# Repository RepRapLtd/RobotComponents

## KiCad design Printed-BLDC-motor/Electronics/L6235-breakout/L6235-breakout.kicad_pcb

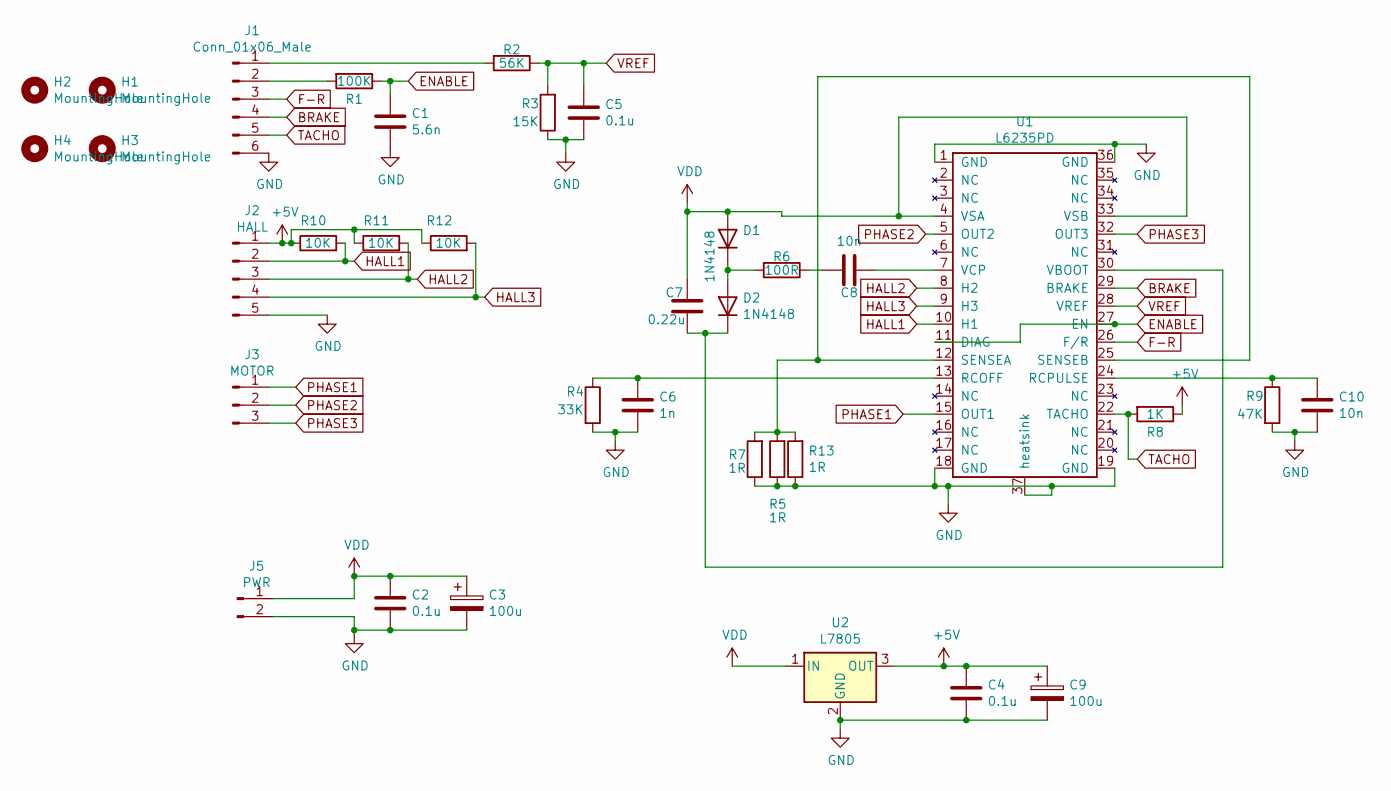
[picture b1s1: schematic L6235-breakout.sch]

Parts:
C1: 5.6n; C_0805_2012Metric
C2, C4, C5: 0.1u; C_0805_2012Metric
C3, C9: 100u; C_Radial_D8.0mm_H7.0mm_P3.50mm
C6: 1n; C_0805_2012Metric
C7: 0.22u; C_0805_2012Metric
C8, C10: 10n; C_0805_2012Metric
D1, D2: 1N4148; D_0805_2012Metric
H1, H2, H3, H4: MountingHole; MountingHole_3.2mm_M3
J1: Conn_01x06_Male; PinHeader_1x06_P2.54mm_Vertical
J2: HALL; PinHeader_1x05_P2.54mm_Vertical
J3: MOTOR; PinHeader_1x03_P2.54mm_Vertical
J5: PWR; PinHeader_1x02_P2.54mm_Vertical
R1: 100K; R_0805_2012Metric
R2: 56K; R_0805_2012Metric
R3: 15K; R_0805_2012Metric
R4: 33K; R_0805_2012Metric
R5, R7, R13: 1R; R_0805_2012Metric
R6: 100R; R_0805_2012Metric
R8: 1K; R_0805_2012Metric
R9: 47K; R_0805_2012Metric
R10, R11, R12: 10K; R_0805_2012Metric
U1: L6235PD; SOIC-36_11mmx16mmx3.6mm
U2: L7805; TO-252-2

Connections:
+5V: C4.1, C9.1, J2.1, R8.1, R10.1, R11.1, R12.1, U2.3 (OUT)
BRAKE: J1.4, U1.29 (BRAKE)
ENABLE: C1.1, R1.1, U1.11 (DIAG), U1.27 (EN)
F-R: J1.3, U1.26 (F/R)
GND: C1.2, C2.2, C3.2, C4.2, C5.2, C6.2, C9.2, C10.2, J1.6, J2.5, J5.2, R3.1, R4.2, R5.1, R7.1, R9.2, R13.1, U1.1 (GND), U1.18 (GND), U1.19 (GND), U1.36 (GND), U1.37 (heatsink), U2.2 (GND)
HALL1: J2.2, R10.2, U1.10 (H1)
HALL2: J2.3, R11.2, U1.8 (H2)
HALL3: J2.4, R12.2, U1.9 (H3)
unnamed: C6.1, R4.1, U1.13 (RCOFF)
unnamed: C7.2, D2.1 (K), U1.30 (VBOOT)
unnamed: C8.1, U1.7 (VCP)
unnamed: C8.2, R6.1
unnamed: C10.1, R9.1, U1.24 (RCPULSE)
unnamed: D1.1 (K), D2.2 (A), R6.2
unnamed: J1.1, R2.2
unnamed: J1.2, R1.2
unnamed: R5.2, R7.2, R13.2, U1.12 (SENSEA), U1.25 (SENSEB)
PHASE1: J3.1, U1.15 (OUT1)
PHASE2: J3.2, U1.5 (OUT2)
PHASE3: J3.3, U1.32 (OUT3)
TACHO: J1.5, R8.2, U1.22 (TACHO)
VDD: C2.1, C3.1, C7.1, D1.2 (A), J5.1, U1.4 (VSA), U1.33 (VSB), U2.1 (IN)
VREF: C5.1, R2.1, R3.2, U1.28 (VREF)

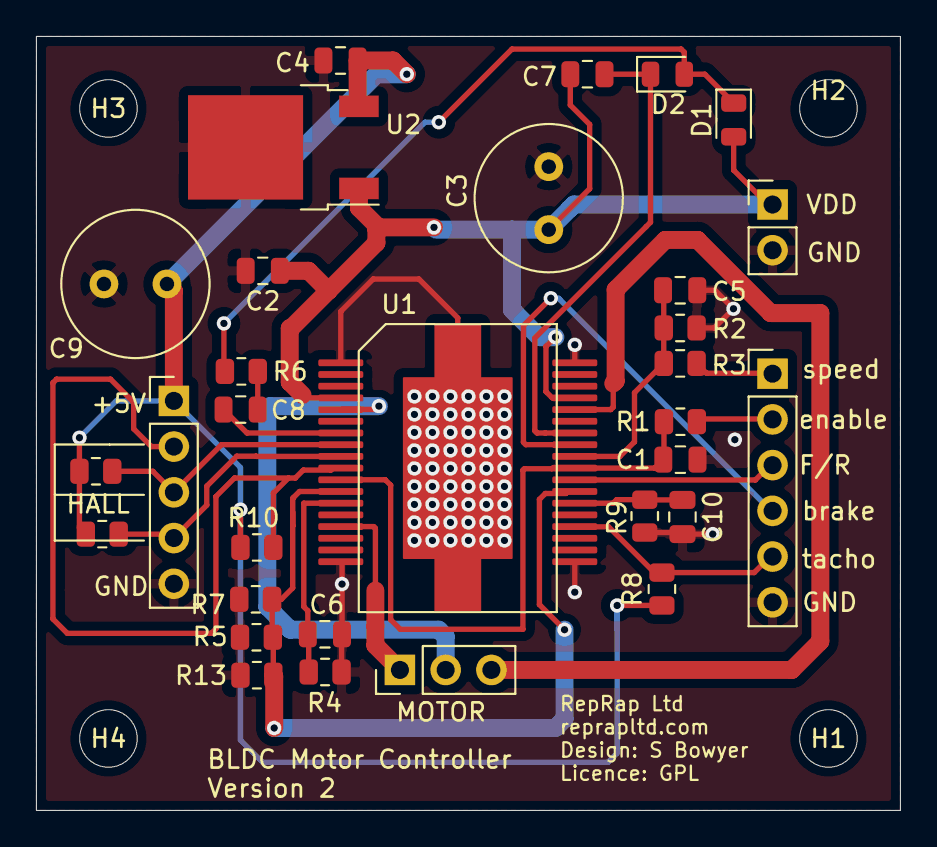
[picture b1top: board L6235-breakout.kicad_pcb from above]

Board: 2 copper layers, 48.0 x 43.0 mm, 35 parts (0 on the bottom side), 23 nets.

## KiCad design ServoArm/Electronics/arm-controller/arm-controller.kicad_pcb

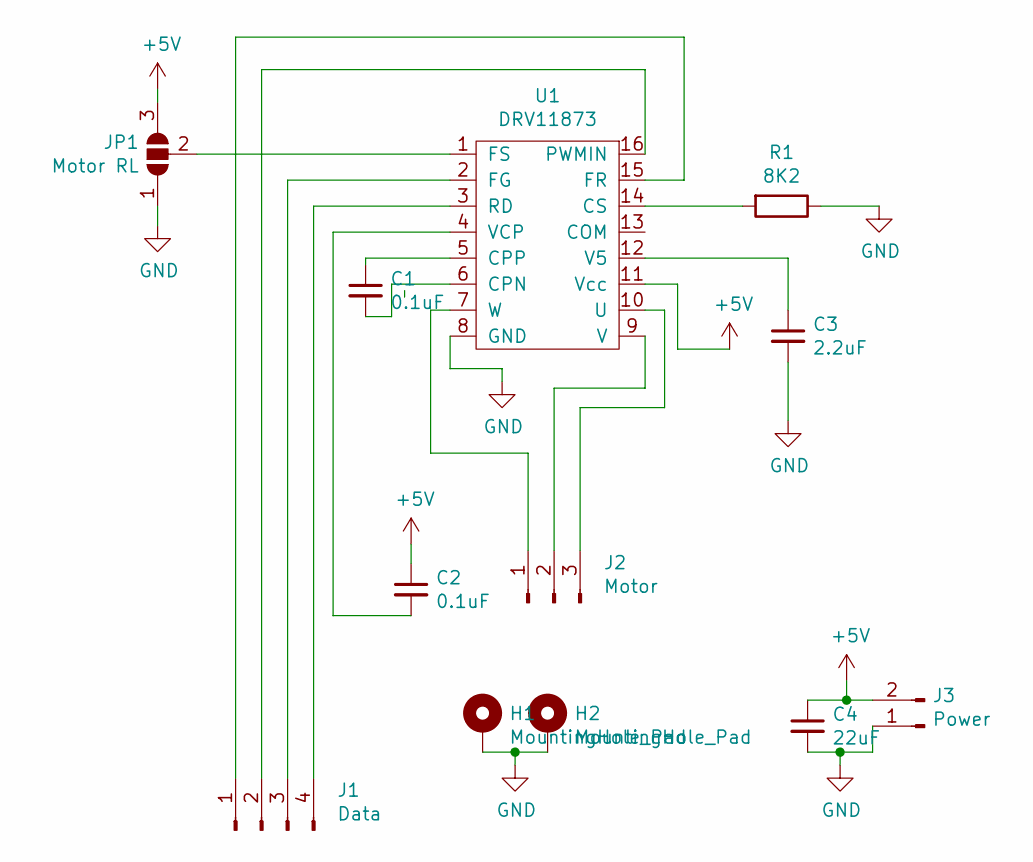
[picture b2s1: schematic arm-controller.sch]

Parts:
C1, C2: 0.1uF; C_0805_2012Metric
C3: 2.2uF; C_0805_2012Metric
C4: 22uF; C_0805_2012Metric
H1, H2: MountingHole_Pad; MountingHole_2.7mm
J1: Data; PinHeader_1x04_P2.54mm_Vertical
J2: Motor; PinHeader_1x03_P2.54mm_Vertical
J3: Power; PinHeader_1x02_P2.54mm_Vertical
JP1: Motor RL; SolderJumper-3_P1.3mm_Open_Pad1.0x1.5mm
R1: 8K2; R_0805_2012Metric
U1: DRV11873; TSSOP-16-1EP_4.4x5mm_P0.65mm

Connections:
+5V: C2.1, C4.1, J3.2, JP1.3 (B), U1.11 (Vcc)
GND: C3.2, C4.2, H1.1, H2.1, J3.1, JP1.1 (A), R1.1, U1.8 (GND)
unnamed: C1.1, U1.5 (CPP)
unnamed: C1.2, U1.6 (CPN)
unnamed: C2.2, U1.4 (VCP)
unnamed: C3.1, U1.12 (V5)
unnamed: J1.1, U1.15 (FR)
unnamed: J1.2, U1.16 (PWMIN)
unnamed: J1.3, U1.2 (FG)
unnamed: J1.4, U1.3 (RD)
unnamed: J2.1, U1.7 (W)
unnamed: J2.2, U1.9 (V)
unnamed: J2.3, U1.10 (U)
unnamed: JP1.2 (C), U1.1 (FS)
unnamed: R1.2, U1.14 (CS)

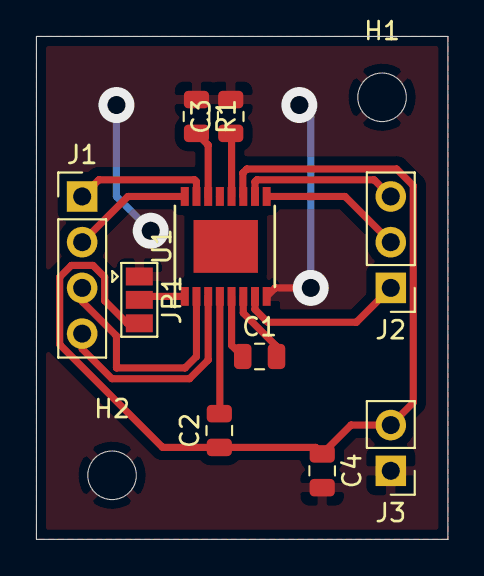
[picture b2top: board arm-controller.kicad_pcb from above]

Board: 2 copper layers, 22.9 x 27.9 mm, 12 parts (0 on the bottom side), 15 nets.

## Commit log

2021-03-15 First commit.
2021-03-16 Corrected gearbox design.
2021-03-17 WIP gearbox and drive.
2021-03-18 WIP.
2021-03-19 Arm WIP.
2021-03-25 First, but not complete, version of the servo.
2021-03-26 First complete (?) servo design.
2021-03-26 Tweaked design...
2021-03-27 Small dimensional adjustments.
2021-03-28 Minor dimension corrections.
2021-03-29 Servo control program started.
2021-03-30 Sally started on a Ravigneaux servo. PID test program WIP.
2021-03-31 Tidyibg the servo program. WIP.
2021-04-01 More rav work (SB). Improved servo prog (AB).
2021-04-13 Various bits of WIP.
2021-04-14 First hack at the printable BLDC motor.
2021-04-27 More details of the BLDC motor completed.
2021-04-29 Added wire drum counter design to measure windings onto the coils.
2021-04-30 First version of coild counter working. Improved sun gear design.
2021-09-29 Playing around with cycloidal gear designs...
2021-09-30 Offset cycloid program coming along. Not yet finished.
2021-09-30 cycloidal drive program fully working
2021-09-30 Further enhancements...
2021-10-01 Blog post files added.
2021-10-01 Comment tidying.
2021-10-01 Spelling...
2021-10-01 More tidying...
2021-10-01 Started design of whole cycloidal gearbox.
2021-10-01 Tidying.
2021-10-02 Started adding code to creat a lip to constrain axial movement.
2021-10-02 Code to optionally create restraining lip added. Seems to work.
2021-10-02 Gearbox changed to take advantage of new code.
2021-10-04 Initial design of motor controller.
2021-10-07 Gearbox and L6235 updates.
2021-10-08 README for cycloidal gearbox.
2021-10-08 Editing README...
2021-10-08 More edits.
2021-10-08 Edit...
2021-10-08 Edit
2021-10-08 Added video
2021-10-15 Latest version of Sally's L6235-breakout
2021-10-20 Latest BLDC driver PCB.
2021-10-27 Added BOM.
2022-01-17 Footprint of TO-220 7805 corrected.
2022-01-18 Controller PCB updated to Version 2.
2022-01-19 Added ground reference to control connector.
2022-01-19 Added Arduino prog for the motor control board.
2022-01-20 Fixed missing chip connetions.
2022-02-09 V2 PCB send for trial production.

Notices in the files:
Printed-BLDC-motor/Electronics/L6235-breakout/L6235-breakout.kicad_pcb:
Licence: GPL
